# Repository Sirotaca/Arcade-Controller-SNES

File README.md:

# Arcade Controller PCB for SNES
PCB for DIY arcade-style controllers for SNES using all through-hole components for ease of hand soldering. An Arduino Nano can optionally be added for input monitoring on a PC using the RetroSpy software. Designed to accept a 20-pin wiring harness using the common Brook UFB pinout.

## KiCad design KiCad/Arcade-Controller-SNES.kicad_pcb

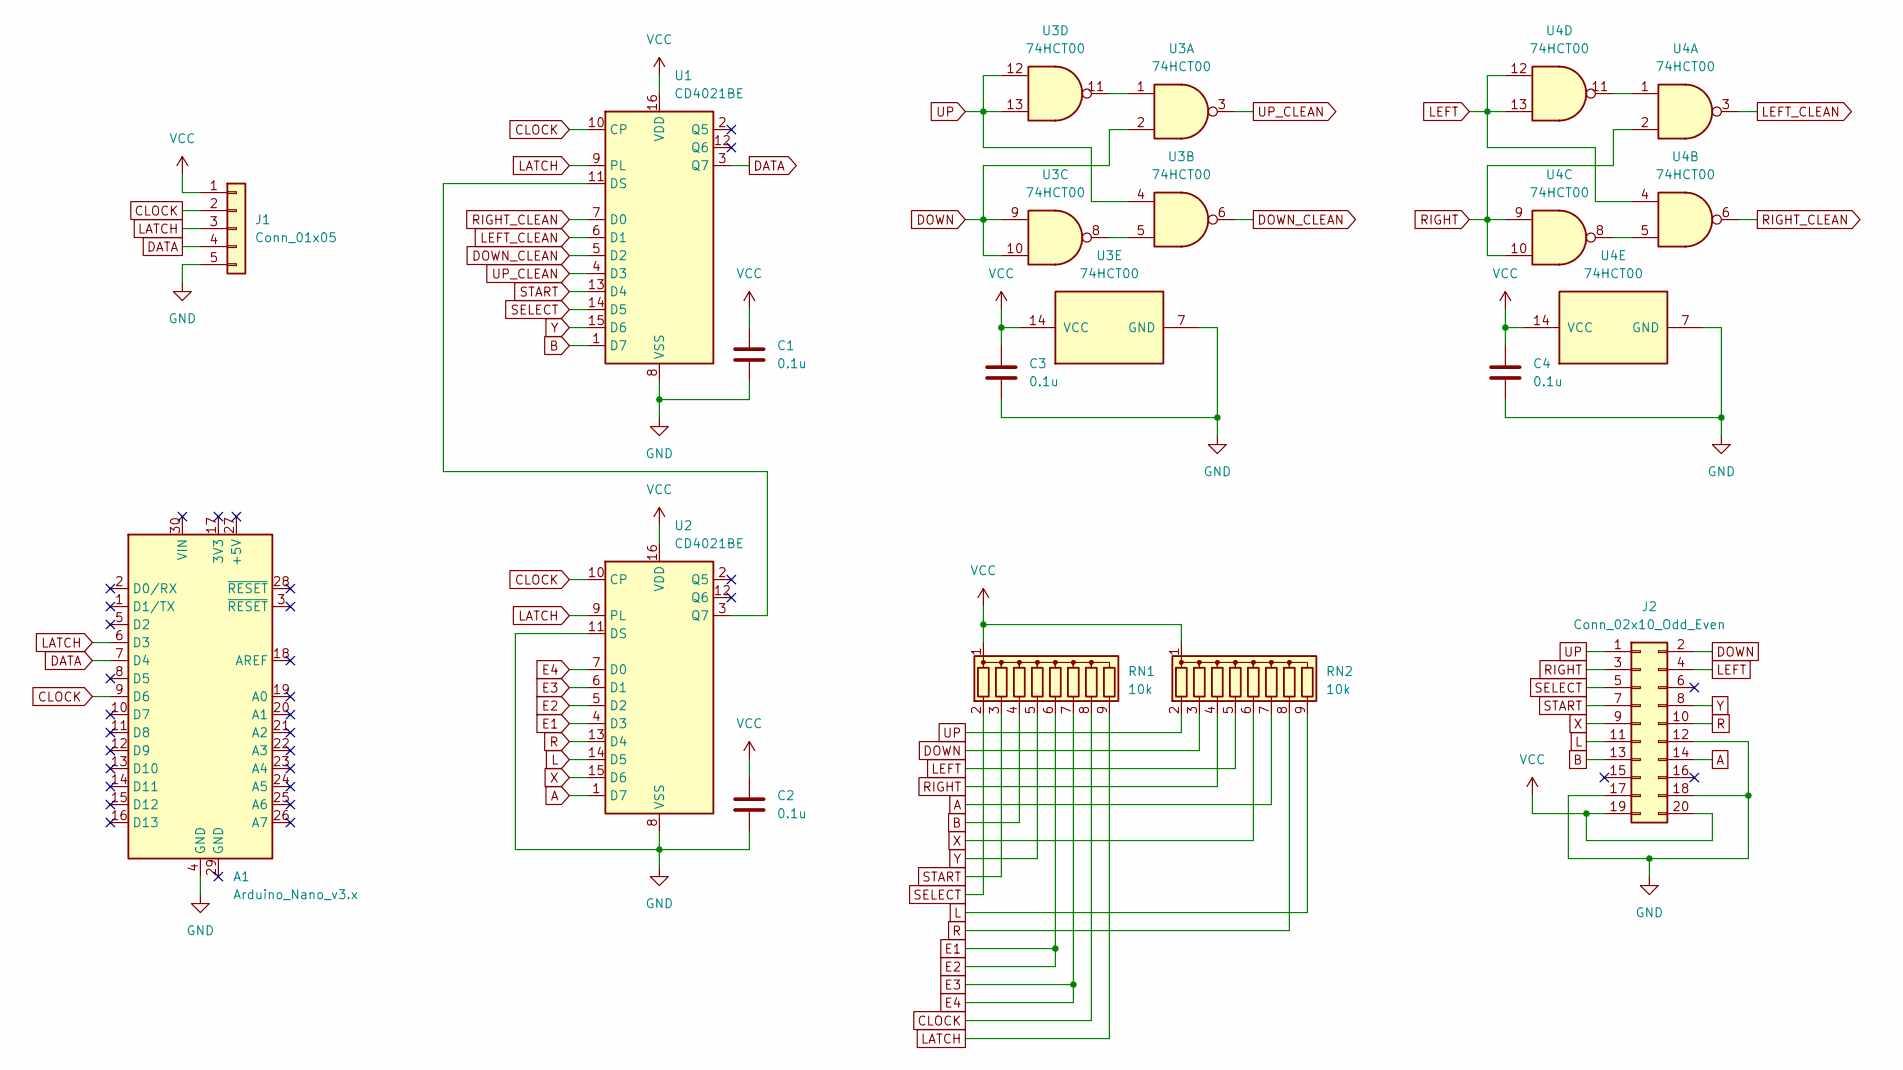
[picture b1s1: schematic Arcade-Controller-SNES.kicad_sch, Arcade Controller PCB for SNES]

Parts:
A1: Arduino_Nano_v3.x; Arduino_Nano
C1, C2, C3, C4: 0.1u; R_Axial_DIN0207_L6.3mm_D2.5mm_P7.62mm_Horizontal
J1: Conn_01x05; PinHeader_1x05_P2.54mm_Vertical
J2: Conn_02x10_Odd_Even; PinHeader_2x10_P2.54mm_Vertical
RN1, RN2: 10k; R_Array_SIP9
U1, U2: CD4021BE; DIP-16_W7.62mm
U3, U4: 74HCT00; DIP-14_W7.62mm

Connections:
A: J2.14, RN2.7 (R6), U2.1 (D7)
B: J2.13, RN1.4 (R3), U1.1 (D7)
CLOCK: A1.9 (D6), J1.2, RN1.8 (R7), U1.10 (CP), U2.10 (CP)
DATA: A1.7 (D4), J1.4, U1.3 (Q7)
DOWN: J2.2, RN2.3 (R2), U3.2, U3.9, U3.10
DOWN_CLEAN: U1.5 (D2), U3.6
E1: RN1.6 (R5), U2.4 (D3), U2.5 (D2)
E3: RN1.7 (R6), U2.6 (D1), U2.7 (D0)
GND: A1.4 (GND), C1.2, C2.2, C3.1, C4.1, J1.5, J2.12, J2.17, J2.18, U1.8 (VSS), U2.8 (VSS), U2.11 (DS), U3.7 (GND), U4.7 (GND)
L: J2.11, RN2.9 (R8), U2.14 (D5)
LATCH: A1.6 (D3), J1.3, RN1.9 (R8), U1.9 (PL), U2.9 (PL)
LEFT: J2.4, RN2.5 (R4), U4.4, U4.12, U4.13
LEFT_CLEAN: U1.6 (D1), U4.3
unnamed: U1.11 (DS), U2.3 (Q7)
unnamed: U3.1, U3.11
unnamed: U3.5, U3.8
unnamed: U4.1, U4.11
unnamed: U4.5, U4.8
R: J2.10, RN2.8 (R7), U2.13 (D4)
RIGHT: J2.3, RN2.4 (R3), U4.2, U4.9, U4.10
RIGHT_CLEAN: U1.7 (D0), U4.6
SELECT: J2.5, RN1.2 (R1), U1.14 (D5)
START: J2.7, RN1.3 (R2), U1.13 (D4)
UP: J2.1, RN2.2 (R1), U3.4, U3.12, U3.13
UP_CLEAN: U1.4 (D3), U3.3
VCC: C1.1, C2.1, C3.2, C4.2, J1.1, J2.19, J2.20, RN1.1 (common), RN2.1 (common), U1.16 (VDD), U2.16 (VDD), U3.14 (VCC), U4.14 (VCC)
X: J2.9, RN2.6 (R5), U2.15 (D6)
Y: J2.8, RN1.5 (R4), U1.15 (D6)

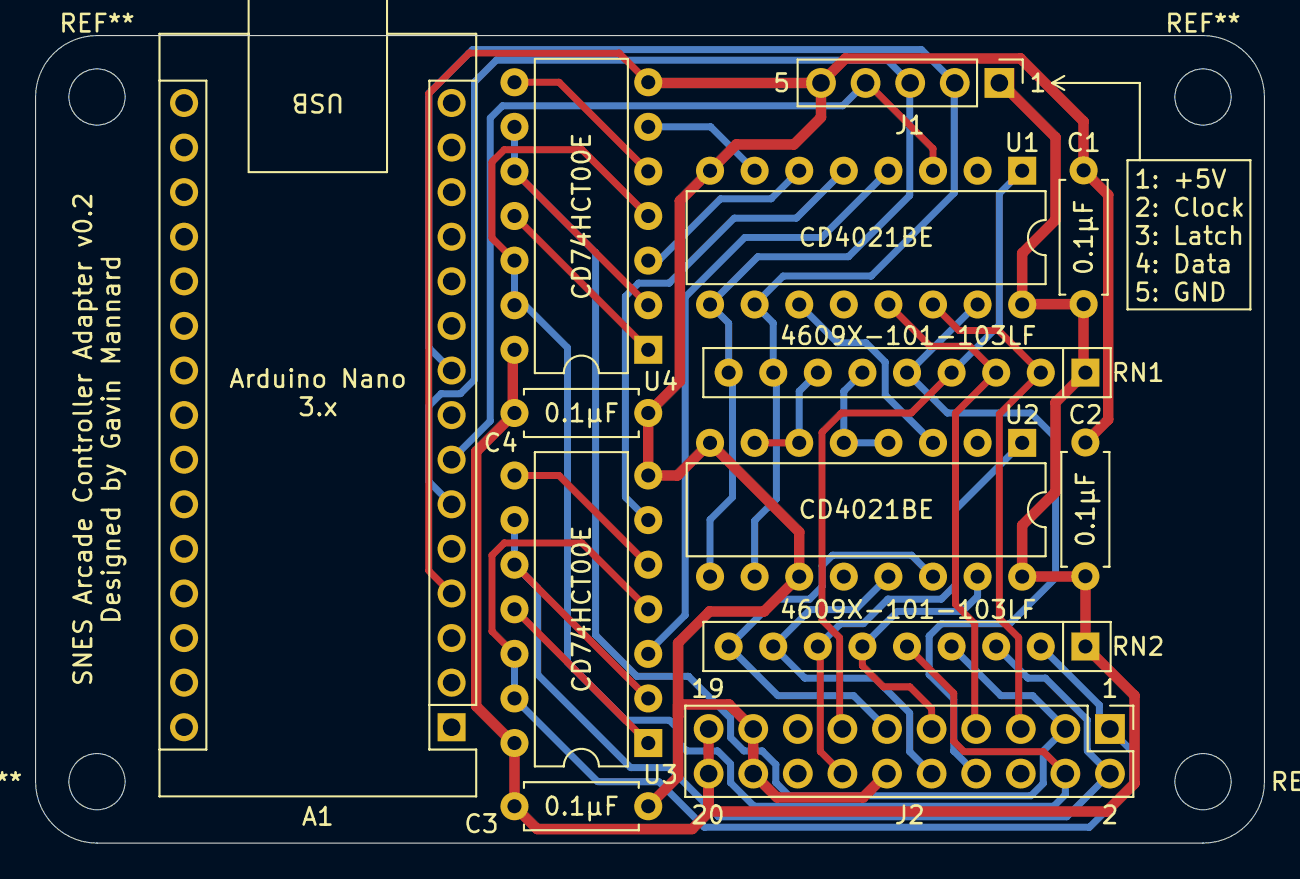
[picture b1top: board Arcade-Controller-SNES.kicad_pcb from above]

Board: 2 copper layers, 70.0 x 46.0 mm, 13 parts (0 on the bottom side), 28 nets.

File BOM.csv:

"Reference","Value","Datasheet","Footprint","Qty","DNP"
"A1","Arduino_Nano_v3.x","http://www.mouser.com/pdfdocs/Gravitech_Arduino_Nano3_0.pdf","Module:Arduino_Nano","1",""
"C1,C2,C3,C4","0.1u","~","Resistor_THT:R_Axial_DIN0207_L6.3mm_D2.5mm_P7.62mm_Horizontal","4",""
"J1","Conn_01x05","~","Connector_PinHeader_2.54mm:PinHeader_1x05_P2.54mm_Vertical","1",""
"J2","Conn_02x10_Odd_Even","~","Connector_PinHeader_2.54mm:PinHeader_2x10_P2.54mm_Vertical","1",""
"RN1,RN2","10k","http://www.vishay.com/docs/31509/csc.pdf","Resistor_THT:R_Array_SIP9","2",""
"U1,U2","CD4021BE","https://assets.nexperia.com/documents/data-sheet/HEF4021B.pdf","Package_DIP:DIP-16_W7.62mm","2",""
"U3,U4","74HCT00","http://www.ti.com/lit/gpn/sn74hct00","Package_DIP:DIP-14_W7.62mm","2",""

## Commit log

2025-05-28 Create LICENSE
